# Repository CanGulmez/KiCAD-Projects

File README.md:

# KiCAD Projects

PCB design projects with KiCAD.

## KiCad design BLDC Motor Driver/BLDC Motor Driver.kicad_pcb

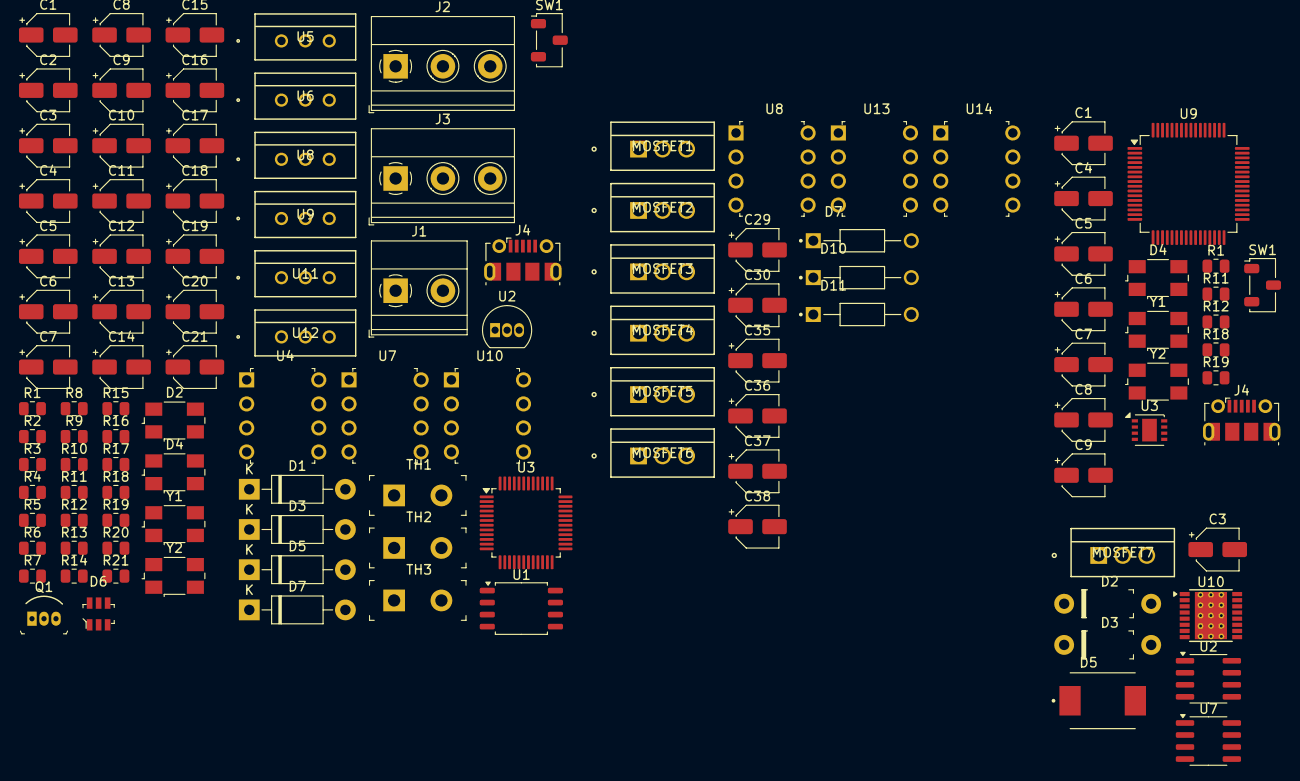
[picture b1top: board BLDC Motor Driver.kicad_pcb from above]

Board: 2 copper layers, 117 parts (0 on the bottom side), 89 nets, no tracks yet.

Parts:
C1, C1#2, C4#2, C7, C8#2: 0.1uF; CP_Elec_4x5.8
C2, C3: 470uF; CP_Elec_4x5.8
C3#2, C5#2, C8, C10, C12, C17, C29, C30, C35, C36, C37, C38: 100nF; CP_Elec_4x5.8
C4: 1nF; CP_Elec_4x5.8
C5, C6, C14, C15: 20pF; CP_Elec_4x5.8
C6#2, C11, C18: 10uF; CP_Elec_4x5.8
C7#2, C9, C19, C20: 10pF; CP_Elec_4x5.8
C9#2, C13, C21: 16uF; CP_Elec_4x5.8
C16: 0u1F; CP_Elec_4x5.8
D1: 1N47xxA; D_DO-41_SOD81_P10.16mm_Horizontal
D2: Q_SCR_AGK; Crystal_SMD_0603-4Pin_6.0x3.5mm
D2#2, D3#2: 1N5817; DO-41
D3, D5, D7: 1N4001; D_DO-41_SOD81_P10.16mm_Horizontal
D4, D4#2: LED; Crystal_SMD_0603-4Pin_6.0x3.5mm
D5#2: MBRS340; DIOM7959X261N
D6: USBLC6-2SC6; SOT23-6L
D7#2, D10, D11: UF4007; DIOAD1036W78L470D235
J1: Screw_Terminal_01x05; TerminalBlock_Phoenix_MKDS-1,5-2_1x02_P5.00mm_Horizontal
J2: Screw_Terminal_01x03; TerminalBlock_Phoenix_MKDS-1,5-3_1x03_P5.00mm_Horizontal
J3: Screw_Terminal_01x02; TerminalBlock_Phoenix_MKDS-1,5-3_1x03_P5.00mm_Horizontal
J4, J4#2: USB_B_Micro; USB_Micro-B_Molex-105017-0001
MOSFET1, MOSFET2, MOSFET3, MOSFET4, MOSFET5, MOSFET6, MOSFET7: IRFB4110PBF; TO-220AB_INF
Q1: 2N7002; TO-92-3
R1, R12, R12#2, R15: 10k; R_0805_2012Metric
R1#2, R2, R3, R8: R; R_0805_2012Metric
R4: 100k; R_0805_2012Metric
R5: 4k; R_0805_2012Metric
R6: 15k; R_0805_2012Metric
R7: 0.01; R_0805_2012Metric
R9: 7k; R_0805_2012Metric
R10: 50k; R_0805_2012Metric
R11, R11#2: 100; R_0805_2012Metric
R13, R14, R16, R17, R20, R21: 10; R_0805_2012Metric
R18, R18#2, R19, R19#2: 22; R_0805_2012Metric
SW1, SW1#2: SW_Push; Nidec_Copal_CAS-120A
TH1, TH2, TH3: 10k; Terminal_Block_D1.3mm_P5mm
U1: LM393; SOP-8_5.28x5.23mm_P1.27mm
U2: TL431LP; TO-92_Inline
U2#2: LM2675M-5; SOIC-8_3.9x4.9mm_P1.27mm
U3: STM32G431C6Tx; LQFP-48_7x7mm_P0.5mm
U3#2: TJA1051TK-3; DFN-8-1EP_3x3mm_P0.65mm_EP1.55x2.4mm
U4, U7, U8, U10, U13, U14: IRS2184; DIP-8_W7.62mm
U5, U6, U8#2, U9, U11, U12: STP100N10F7; TO_0N10F7_STM
U7#2: LM2675M-3.3; SOIC-8_3.9x4.9mm_P1.27mm
U9#2: STM32F446RETx; LQFP-64_10x10mm_P0.5mm
U10#2: LM5088-1; HTSSOP-16-1EP_4.4x5mm_P0.65mm_EP3.4x5mm_Mask3x3mm_ThermalVi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
Y1: 24MHz; Crystal_SMD_0603-4Pin_6.0x3.5mm
Y1#2: 16MHz; Crystal_SMD_0603-4Pin_6.0x3.5mm
Y2, Y2#2: 32.768kHZ; Crystal_SMD_0603-4Pin_6.0x3.5mm

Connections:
+3.3V: C1.1, C4#2.1, C7.1, C8.1, C8#2.1, C12.1, R10.2, R12.2, R12#2.2, TH1.2, TH2.2, TH3.2, U3.1 (VBAT), U3.21 (VDDA), U3.24 (VDD), U3.36 (VDD), U3.48 (VDD), U3#2.5 (VIO), U7#2.4 (FB), U9#2.1 (VBAT), U9#2.13 (VDDA), U9#2.19 (VDD), U9#2.32 (VDD), U9#2.48 (VDD), U9#2.64 (VDD)
+5V: C16.1, D6.2, J4.1 (VBUS), J4#2.1 (VBUS), U2#2.4 (FB), U3#2.3 (VCC), U7#2.5 (ON/~OFF), U7#2.7 (VIN)
+12V: C29.1, C35.1, C37.1, D7#2.A, D10.A, D11.A, U2#2.7 (VIN), U8.5 (VCC), U10#2.9 (OUT), U13.5 (VCC), U14.5 (VCC)
/BOOT0: R1.2, U9#2.60 (BOOT0)
/CAN_RX: U3#2.4 (RXD), U9#2.57 (PB5(CAN2_RX))
/CAN_TX: U3#2.1 (TXD), U9#2.58 (PB6(CAN2_TX))
/HAL_A: J1.1, U9#2.37 (PC6)
/HAL_B: J1.2, U9#2.38 (PC7)
/LED_RED: R11.2, U9#2.26 (PB0)
/MAIN_SUPP: C3#2.1, J3.1, MOSFET1.2 (D), MOSFET3.2 (D), MOSFET5.2 (D), MOSFET7.2 (D), U10#2.1 (VIN)
/NRST: R12#2.1, SW1.2, U9#2.7 (NRST)
/OSC32_IN: C7#2.1, U9#2.3 (PC14(OSC32_IN)), Y2#2.1
/OSC32_OUT: C9.1, U9#2.4 (PC15(OSC32_OUT)), Y2#2.2
/OSC_IN: C5.1, U9#2.5 (PH0(OSC_IN)), Y1#2.2
/OSC_OUT: C6.1, U9#2.6 (PH1(OSC_OUT)), Y1#2.1
/PWM_A: U8.1 (IN), U9#2.41 (PA8(TIM1_CH1))
/PWM_B: U9#2.42 (PA9(TIM1_CH2)), U13.1 (IN)
/PWM_C: U9#2.43 (PA10(TIM1_CH3)), U14.1 (IN)
/PowerStage/Phase_A: C30.2, MOSFET1.3 (S), MOSFET2.2 (D), U8.6 (VS)
/PowerStage/Phase_B: C36.2, MOSFET3.3 (S), MOSFET4.2 (D), U13.6 (VS)
/PowerStage/Phase_C: C38.2, MOSFET5.3 (S), MOSFET6.2 (D), U14.6 (VS)
/SD_A: U8.2 (~SD), U9#2.51 (PC10)
/SD_B: U9#2.52 (PC11), U13.2 (~SD)
/SD_C: U9#2.53 (PC12), U14.2 (~SD)
/USB_DM: R19.1, U9#2.44 (PA11(OTG_DM))
/USB_DP: R18#2.2, U9#2.45 (PA12(OTG_DP))
BOOT0: R15.2, U3.45 (PB8)
ESD_DM: D6.3, R19#2.1
ESD_DP: D6.1, R18.2
GND: C1.2, C1#2.2, C2.2, C3.2, C3#2.2, C4.2, C4#2.2, C5.2, C6.2, C6#2.2, C7.2, C7#2.2, C8.2, C8#2.2, C9.2, C11.2, C12.2, C14.2, C15.2, C16.2, C18.2, C20.2, C29.2, C35.2, C37.2, D1.2 (A), D2.3 (K), D2#2.A, D3#2.A, D4.1 (K), D4#2.1 (K), D6.5, J3.2, J4.4 (ID), J4.5 (GND), J4.6 (Shield), J4#2.4 (ID), J4#2.5 (GND), J4#2.6 (Shield), Q1.1 (S), R1#2.1, R3.1, R5.2, R7.2, R8.1, R9.2, SW1.1, SW1#2.1, U2.2 (A), U2#2.6 (GND), U3.19 (VSSA), U3.23 (VSS), U3.35 (VSS), U3.47 (VSS), U3#2.2 (GND), U3#2.8 (S), U3#2.9 (GND), U4.3 (COM), U7.3 (COM), U8.3 (COM), U9#2.12 (VSSA), U9#2.18 (VSS), U9#2.31 (VSS), U9#2.47 (VSS), U9#2.63 (VSS), U10.3 (COM), U10#2.4 (RAMP), U10#2.6 (GND), U10#2.11 (CSG), U10#2.17 (PGND), U13.3 (COM), U14.3 (COM)
LED_RED: R11#2.2, U3.29 (PB15)
NRST: R12.1, SW1#2.2, U3.7 (PG10)
NTC_A: R8.2, TH3.1, U3.10 (PA2)
NTC_B: R3.2, TH2.1, U3.11 (PA3)
NTC_C: R1#2.2, TH1.1, U3.17 (PB1)
unnamed: C5#2.2, C6#2.1
unnamed: C10.2, C11.1
unnamed: C17.2, C18.1
unnamed: D1.1 (K), R2.2, U1.1
unnamed: D2.2 (G), R6.2, U2.3 (K)
unnamed: C9#2.1, D3.1 (K), U4.8 (VB)
unnamed: D4.2 (A), D4#2.2 (A), R11.1, R11#2.1
unnamed: C13.1, D5.1 (K), U7.8 (VB)
unnamed: C21.1, D7.1 (K), U10.8 (VB)
unnamed: J4.3 (D+), J4#2.3 (D+), R18.1, R18#2.1
unnamed: J4.2 (D-), J4#2.2 (D-), R19.2, R19#2.2
unnamed: MOSFET7.1 (G), U10#2.14 (HG)
unnamed: D5#2.C, MOSFET7.3 (S), U10#2.13 (SW)
unnamed: Q1.2 (G), R2.1
unnamed: R1.1, R15.1
unnamed: R9.1, R10.1, U1.2 (-)
unnamed: R4.2, R5.1, U2.1 (REF)
unnamed: D2#2.K, U2#2.8 (VSW)
unnamed: R13.2, U5.1 (G)
unnamed: R14.2, U6.1 (G)
unnamed: D3#2.K, U7#2.8 (VSW)
unnamed: R16.2, U8#2.1 (G)
unnamed: C30.1, D7#2.C, U8.8 (VB)
unnamed: R17.2, U9.1 (G)
unnamed: D5#2.A, U10#2.12 (CS)
unnamed: R20.2, U11.1 (G)
unnamed: R21.2, U12.1 (G)
unnamed: C36.1, D10.C, U13.8 (VB)
unnamed: C38.1, D11.C, U14.8 (VB)
OCP: C4.1, R7.1, U1.3 (+), U6.3 (S), U9.3 (S), U12.3 (S)
OCP_R: Q1.3 (D), U3.39 (PA15)
OSC32_IN: C19.1, U3.3 (PC14), Y2.1
OSC32_OUT: C20.1, U3.4 (PC15), Y2.2
OSC_IN: C14.1, U3.5 (PF0), Y1.2
OSC_OUT: C15.1, U3.6 (PF1), Y1.1
OVP: C1#2.1, C2.1, C3.1, D2.1 (A), R4.1, R6.1, U5.2 (D), U8#2.2 (D), U11.2 (D)
PWM_A: U3.15 (PA7), U4.1 (IN)
PWM_B: U3.30 (PA8), U7.1 (IN)
PWM_C: U3.31 (PA9), U10.1 (IN)
Phase_A: C9#2.2, J2.1, U4.6 (VS), U5.3 (S), U6.2 (D)
Phase_A_H: R13.1, U4.7 (HO)
Phase_A_L: R14.1, U4.4 (LO)
Phase_A_SD: U3.22 (PB10), U4.2 (~SD)
Phase_B: C13.2, J2.2, U7.6 (VS), U8#2.3 (S), U9.2 (D)
Phase_B_H: R16.1, U7.7 (HO)
Phase_B_L: R17.1, U7.4 (LO)
Phase_B_SD: U3.25 (PB11), U7.2 (~SD)
Phase_C: C21.2, J2.3, U10.6 (VS), U11.3 (S), U12.2 (D)
Phase_C_H: R20.1, U10.7 (HO)
Phase_C_L: R21.1, U10.4 (LO)
Phase_C_SD: U3.26 (PB12), U10.2 (~SD)
USB_DM: D6.4, U3.33 (PA11)
USB_DP: D6.6, U3.34 (PA12)
VCC: C5#2.1, C10.1, C17.1, D3.2 (A), D5.2 (A), D7.2 (A), U4.5 (VCC), U7.5 (VCC), U10.5 (VCC)

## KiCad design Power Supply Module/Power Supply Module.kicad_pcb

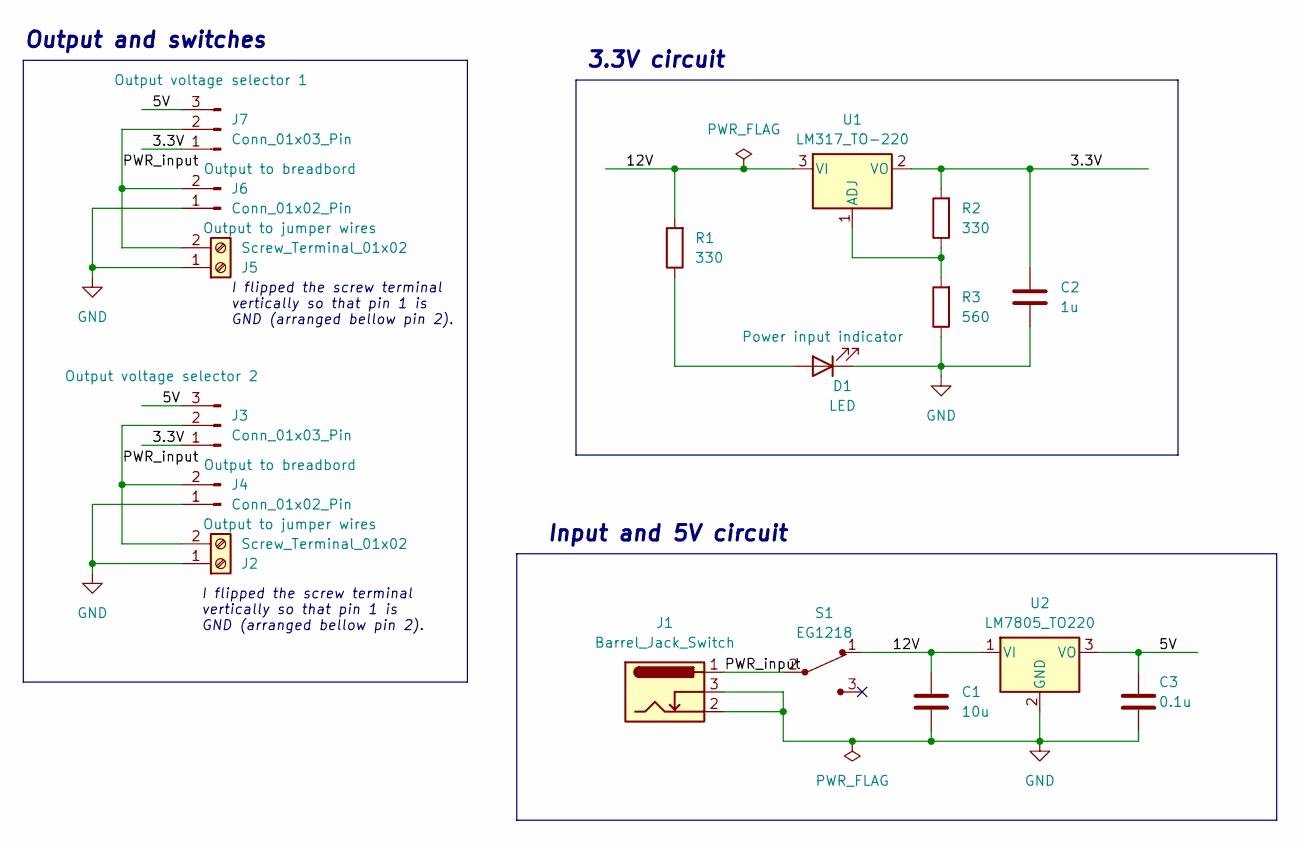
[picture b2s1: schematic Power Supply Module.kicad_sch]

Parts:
C1: 10u; C_Disc_D3.0mm_W1.6mm_P2.50mm
C2: 1u; C_Disc_D3.0mm_W1.6mm_P2.50mm
C3: 0.1u; C_Disc_D3.0mm_W1.6mm_P2.50mm
D1: LED; LED_D5.0mm
J1: Barrel_Jack_Switch; BarrelJack_Horizontal
J2, J5: Screw_Terminal_01x02; TerminalBlock_bornier-2_P5.08mm
J3, J7: Conn_01x03_Pin; PinHeader_1x03_P2.54mm_Vertical
J4, J6: Conn_01x02_Pin; PinHeader_1x02_P2.54mm_Vertical
R1, R2: 330; R_Axial_DIN0204_L3.6mm_D1.6mm_P7.62mm_Horizontal
R3: 560; R_Axial_DIN0204_L3.6mm_D1.6mm_P7.62mm_Horizontal
S1: EG1218; Switch_Slide_11.6x4mm_EG1218; MPN EG1218; Digi-Key_PN EG1903-ND
U1: LM317_TO-220; TO-220-3_Vertical
U2: LM7805_TO220; TO-220-3_Vertical

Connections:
/3.3V: C2.1, J3.1, J7.1, R2.2, U1.2 (VO)
/5V: C3.1, J3.3, J7.3, U2.3 (VO)
/12V: C1.1, R1.2, S1.1, U1.3 (VI), U2.1 (VI)
/PWR_input: J1.1, J2.2, J3.2, J4.2, J5.2, J6.2, J7.2, S1.2
GND: C1.2, C2.2, C3.2, D1.1 (K), J1.2, J1.3, J2.1, J4.1, J5.1, J6.1, R3.1, U2.2 (GND)
unnamed: D1.2 (A), R1.1
unnamed: R2.1, R3.2, U1.1 (ADJ)

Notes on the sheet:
Input and 5V circuit
Output and switches
3.3V circuit
I flipped the screw terminal vertically so that pin 1 is GND (arranged bellow pin 2).

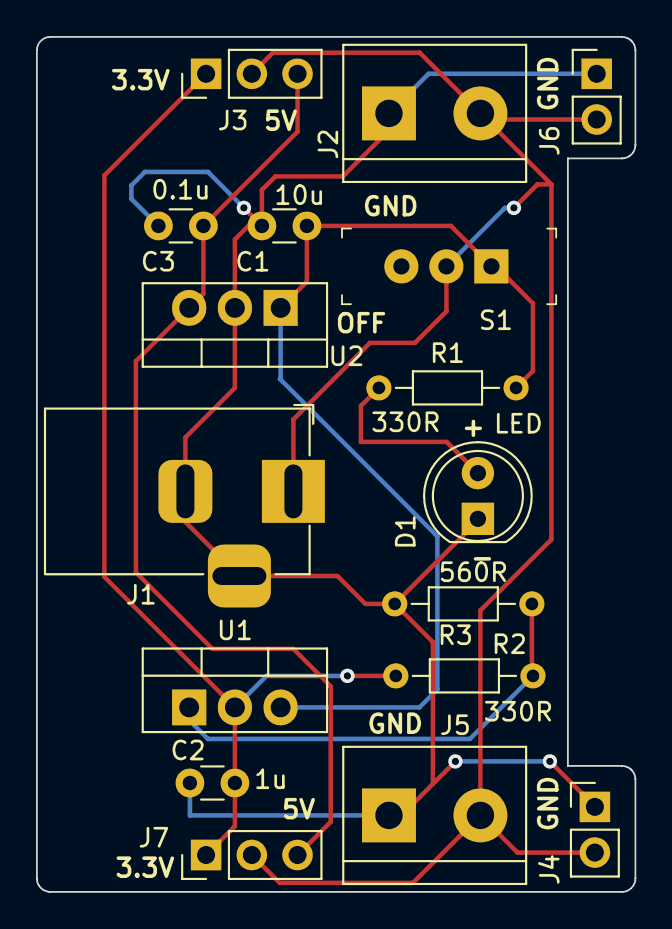
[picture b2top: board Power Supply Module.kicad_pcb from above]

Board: 2 copper layers, 33.2 x 47.5 mm, 17 parts (0 on the bottom side), 7 nets.

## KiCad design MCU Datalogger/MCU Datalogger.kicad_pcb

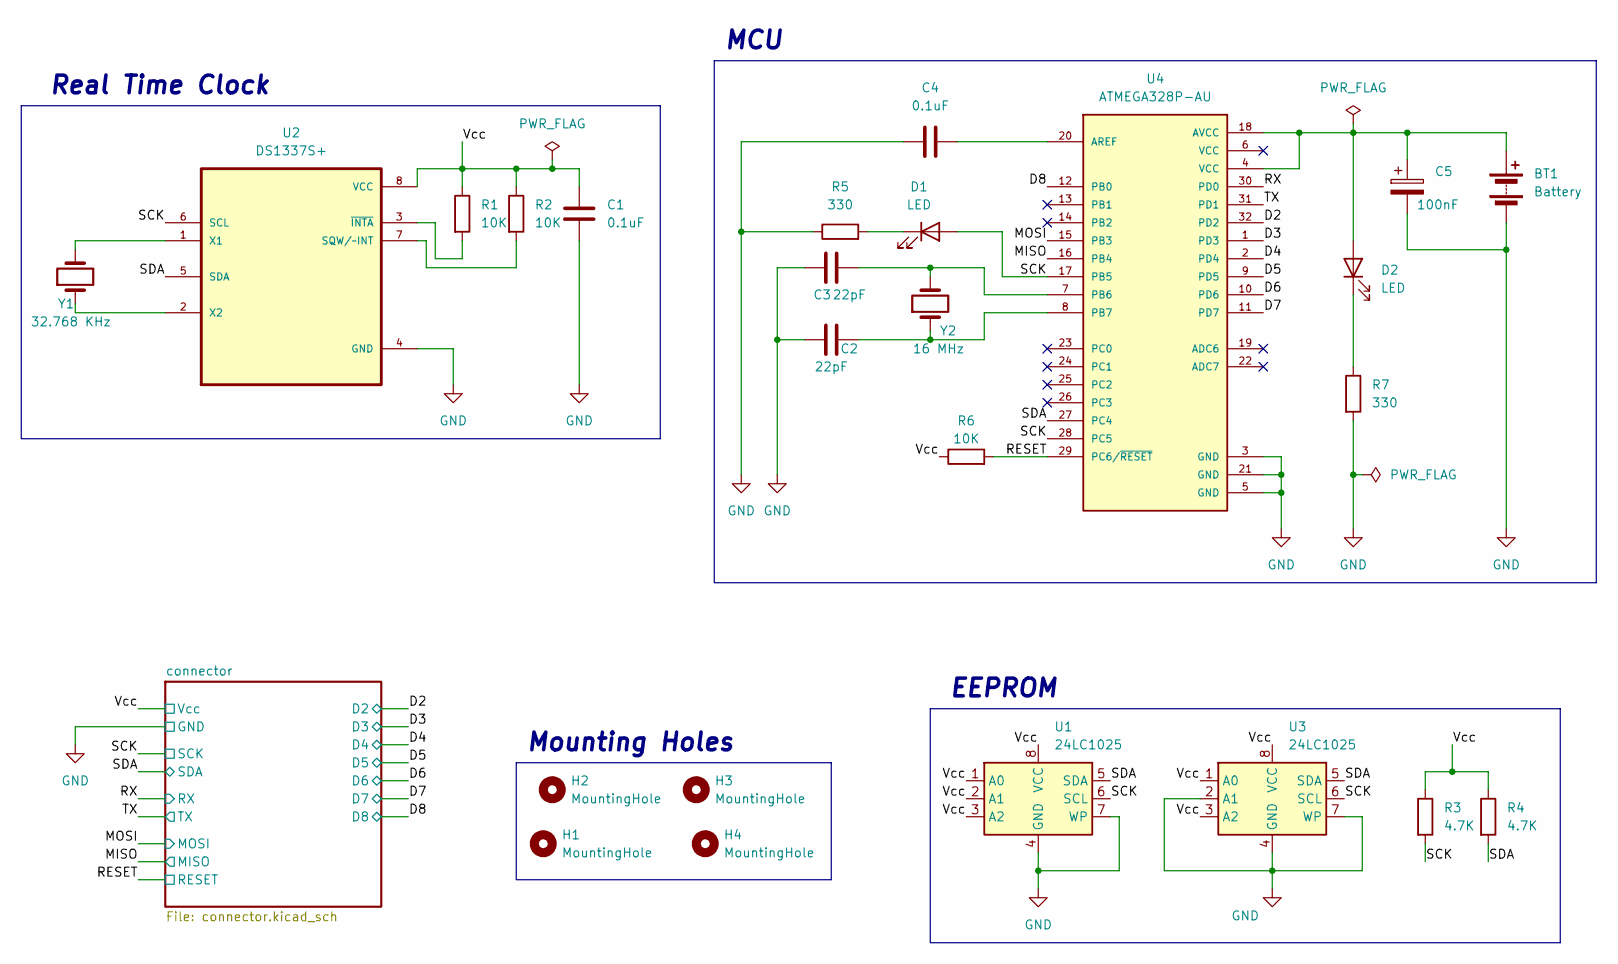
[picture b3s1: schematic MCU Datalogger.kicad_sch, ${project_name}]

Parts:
BT1: Battery; PinHeader_1x02_P2.54mm_Vertical
C1, C4: 0.1uF; C_0805_2012Metric
C2, C3: 22pF; C_0805_2012Metric
C5: 100nF; C_0805_2012Metric
D1, D2: LED; LED_0805_2012Metric
H1, H2, H3, H4: MountingHole; MountingHole_2.1mm
R1, R2, R6: 10K; R_0805_2012Metric
R3, R4: 4.7K; R_0805_2012Metric
R5, R7: 330; R_0805_2012Metric
U1, U3: 24LC1025; SOIC-8_5.23x5.23mm_P1.27mm
U2: DS1337S+; SOIC127P600X175-8N
U4: ATMEGA328P-AU; QFP80P900X900X120-32N; PARTREV 8271A
Y1: 32.768 KHz; Crystal_SMD_5032-2Pin_5.0x3.2mm_HandSoldering
Y2: 16 MHz; Crystal_SMD_5032-2Pin_5.0x3.2mm_HandSoldering

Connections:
/D2: U4.32 (PD2); also elsewhere on the board
/D3: U4.1 (PD3); also elsewhere on the board
/D4: U4.2 (PD4); also elsewhere on the board
/D5: U4.9 (PD5); also elsewhere on the board
/D6: U4.10 (PD6); also elsewhere on the board
/D7: U4.11 (PD7); also elsewhere on the board
/D8: U4.12 (PB0); also elsewhere on the board
/MISO: U4.16 (PB4); also elsewhere on the board
/MOSI: U4.15 (PB3); also elsewhere on the board
/RESET: R6.2, U4.29 (PC6/~RESET); also elsewhere on the board
/RX: U4.30 (PD0); also elsewhere on the board
/SCK: D1.2 (A), R3.2, U1.6 (SCL), U2.6 (SCL), U3.6 (SCL), U4.17 (PB5), U4.28 (PC5); also elsewhere on the board
/SDA: R4.2, U1.5 (SDA), U2.5 (SDA), U3.5 (SDA), U4.27 (PC4); also elsewhere on the board
/TX: U4.31 (PD1); also elsewhere on the board
/Vcc: C1.1, R1.1, R2.1, R3.1, R4.1, R6.1, U1.1 (A0), U1.2 (A1), U1.3 (A2), U1.8 (VCC), U2.8 (VCC), U3.1 (A0), U3.3 (A2), U3.8 (VCC); also elsewhere on the board
GND: BT1.2 (-), C1.2, C2.1, C3.1, C4.1, C5.2, R5.1, R7.2, U1.4 (GND), U1.7 (WP), U2.4 (GND), U3.2 (A1), U3.4 (GND), U3.7 (WP), U4.3 (GND), U4.5 (GND), U4.21 (GND); also elsewhere on the board
unnamed: BT1.1 (+), C5.1, D2.2 (A), U4.4 (VCC), U4.18 (AVCC)
unnamed: D1.1 (K), R5.2
unnamed: D2.1 (K), R7.1
unnamed: R2.2, U2.7 (SQW/~INT)
unnamed: U2.1 (X1), Y1.2
unnamed: U2.2 (X2), Y1.1
unnamed: R1.2, U2.3 (~INTA)
unnamed: C4.2, U4.20 (AREF)
unnamed: C3.2, U4.7 (PB6), Y2.2
unnamed: C2.2, U4.8 (PB7), Y2.1

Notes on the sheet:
MCU
EEPROM
Real Time Clock
Mounting Holes

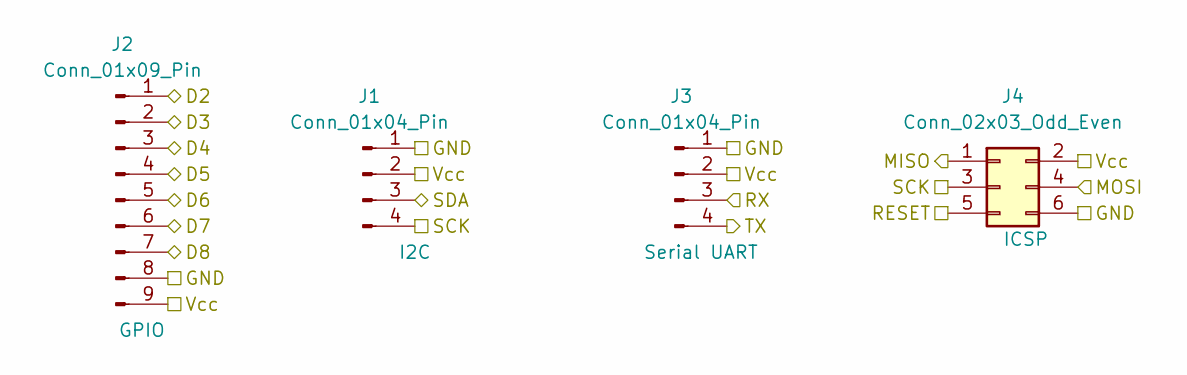
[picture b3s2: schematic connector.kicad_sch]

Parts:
J1, J3: Conn_01x04_Pin; PinHeader_1x04_P2.54mm_Vertical
J2: Conn_01x09_Pin; PinHeader_1x09_P2.54mm_Vertical
J4: Conn_02x03_Odd_Even; PinHeader_2x03_P2.54mm_Vertical

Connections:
/D2: J2.1; also elsewhere on the board
/D3: J2.2; also elsewhere on the board
/D4: J2.3; also elsewhere on the board
/D5: J2.4; also elsewhere on the board
/D6: J2.5; also elsewhere on the board
/D7: J2.6; also elsewhere on the board
/D8: J2.7; also elsewhere on the board
/MISO: J4.1; also elsewhere on the board
/MOSI: J4.4; also elsewhere on the board
/RESET: J4.5; also elsewhere on the board
/RX: J3.3; also elsewhere on the board
/SCK: J1.4, J4.3; also elsewhere on the board
/SDA: J1.3; also elsewhere on the board
/TX: J3.4; also elsewhere on the board
/Vcc: J1.2, J2.9, J3.2, J4.2; also elsewhere on the board
GND: J1.1, J2.8, J3.1, J4.6; also elsewhere on the board

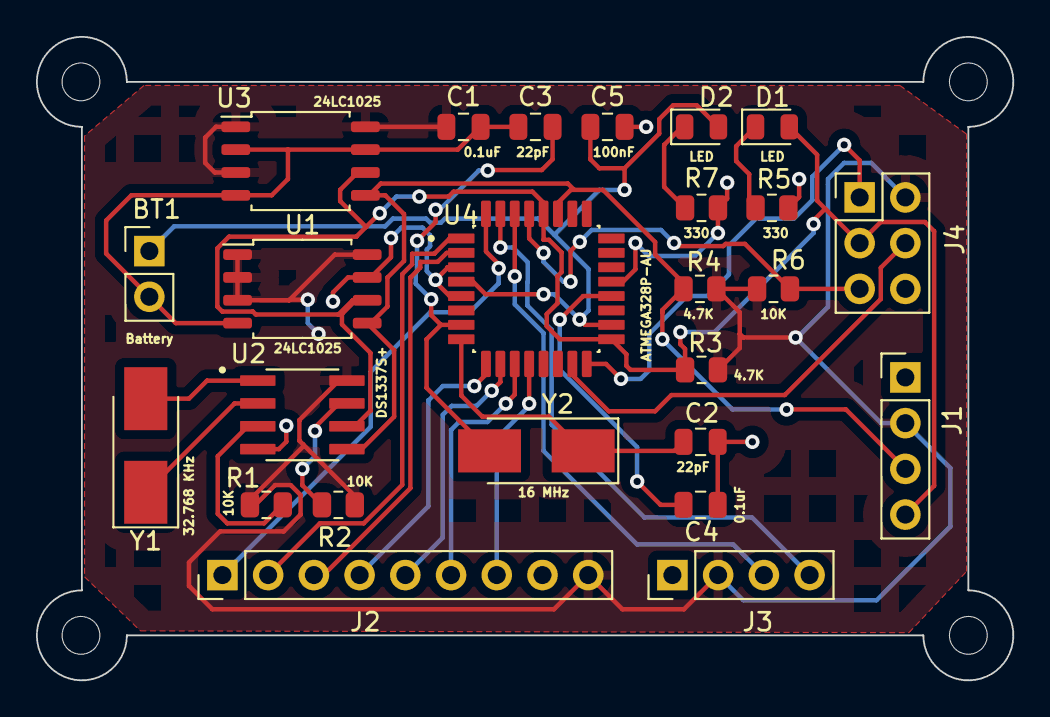
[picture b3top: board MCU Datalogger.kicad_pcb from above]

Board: 2 copper layers, 54.2 x 35.7 mm, 29 parts (0 on the bottom side), 26 nets.

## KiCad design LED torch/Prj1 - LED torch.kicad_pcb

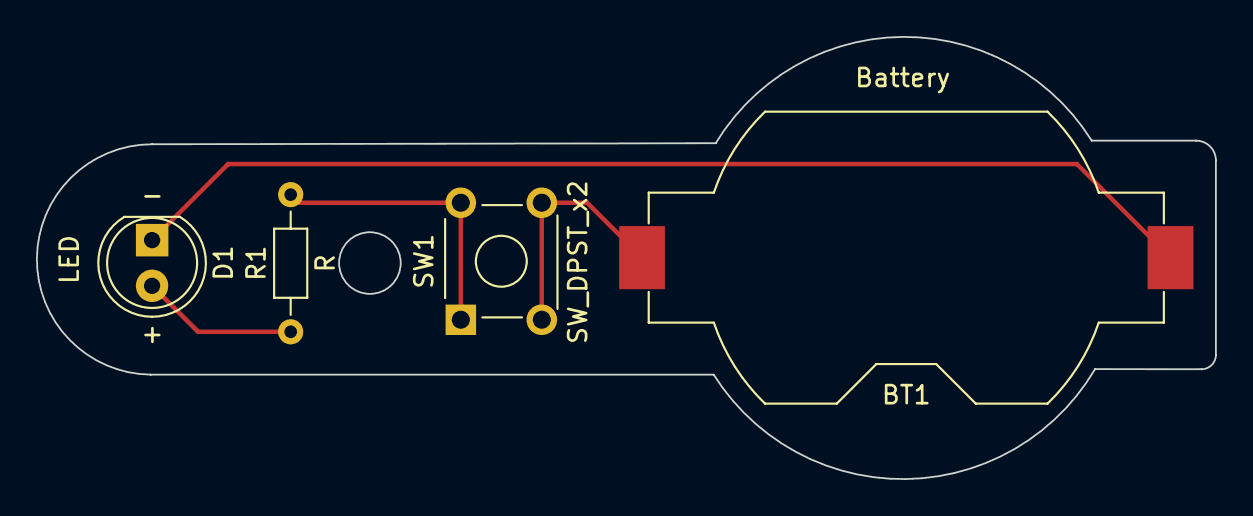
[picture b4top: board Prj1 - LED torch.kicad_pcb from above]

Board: 2 copper layers, 65.5 x 24.6 mm, 4 parts (0 on the bottom side), 4 nets.

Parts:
BT1: Battery; BatteryHolder_Keystone_1058_1x2032
D1: LED; LED_D5.0mm
R1: R; R_Axial_DIN0204_L3.6mm_D1.6mm_P7.62mm_Horizontal
SW1: SW_DPST_x2; SW_TH_Tactile_Omron_B3F-10xx

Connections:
/Bettery_pos: BT1.1 (+), SW1.2 (B)
/LED_anode: D1.2 (A), R1.1
/LED_cathode: BT1.2 (-), D1.1 (K)
unnamed: R1.2, SW1.1 (A)
